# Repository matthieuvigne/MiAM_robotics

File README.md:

# MiAM_robotics

This repo contains information and software for robotic-related projects done with the [MiAM Eurobot team](https://www.miam-robotique.fr/).

Our robot architecture are based off an embedded linux on an ARM platform, Raspberry Pi or Beaglebone Black, programmed
in C++. We also use Arduinos as slaves for low-level tasks such as motor control or sensor handling - using serial communication through
USB.

## Folder structure

 - [miam_utils](./miam_utils) : a very generic C++ library for handling all low-level activities. This ranges from sensor drivers to
 basic robot functions such as PID or basic data logging. This is the base code from which other projects spawn.
 Feel free to use this code in other projects !
 
 - [vacuum_cleaning](./vacuum_cleaning) : our current project, a vacuum-cleaning omnidirectional robot.

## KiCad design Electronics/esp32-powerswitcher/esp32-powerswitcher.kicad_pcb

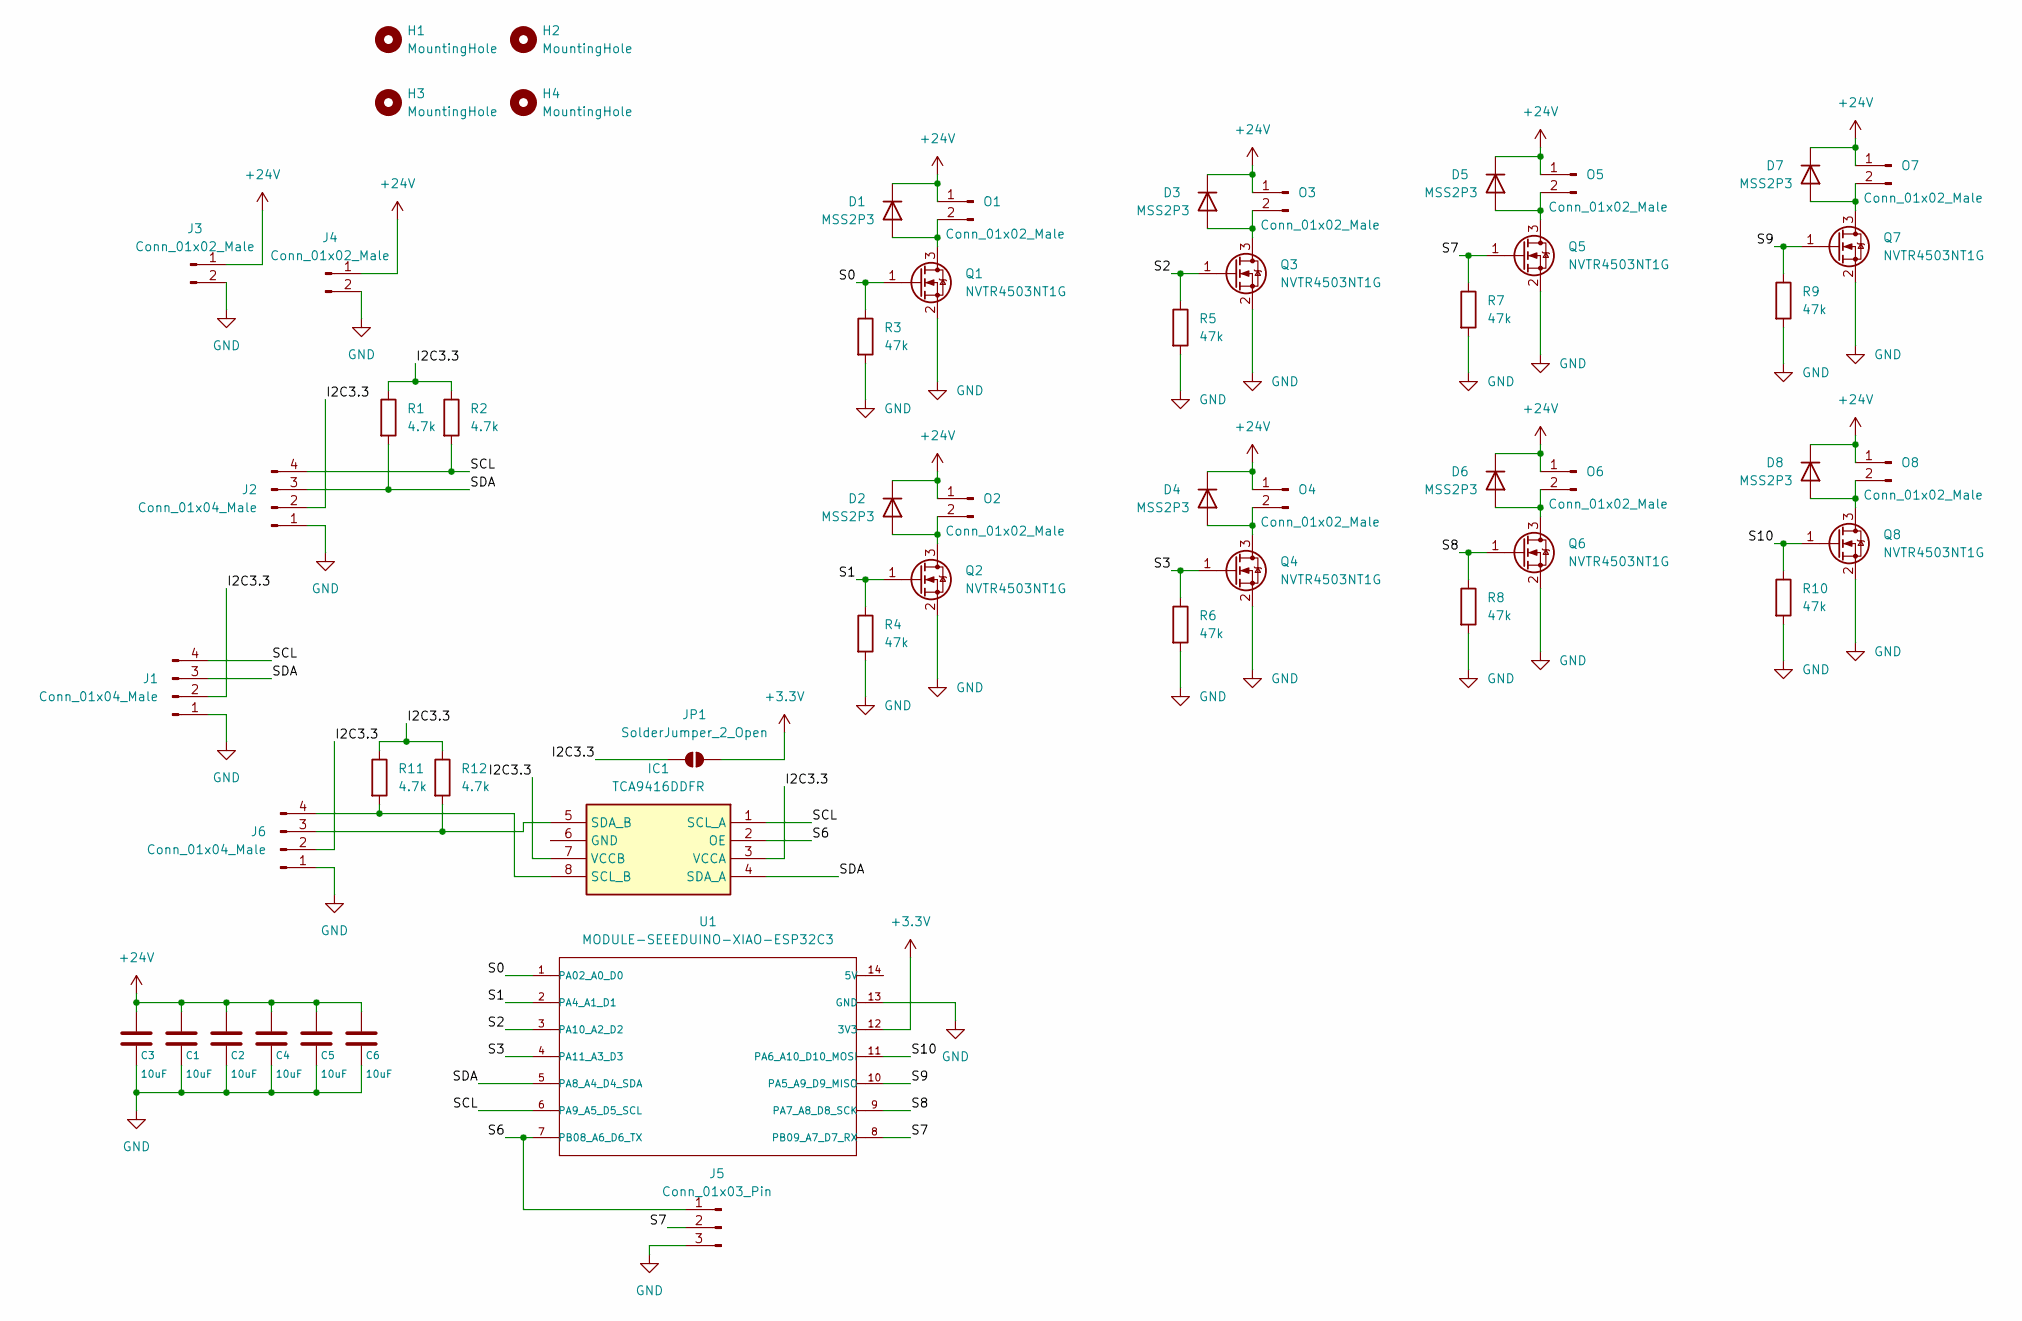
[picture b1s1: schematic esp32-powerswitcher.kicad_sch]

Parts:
C1, C2, C3, C4, C5, C6: 10uF; C_1206_3216Metric_Pad1.33x1.80mm_HandSolder; MPN CL31A106MBHNNNE; Mouser Part Number 187-CL31A106MBHNNNE
D1, D2, D3, D4, D5, D6, D7, D8: MSS2P3; D_MicroSMP_AK
H1, H2, H3, H4: MountingHole; MountingHole_3.2mm_M3
IC1: TCA9416DDFR; SOT65P280X110-8N; Manufacturer_Part_Number TCA9416DDFR; Mouser Part Number 595-TCA9416DDFR
J1, J2, J6: Conn_01x04_Male; JST_SH_SM04B-SRSS-TB_1x04-1MP_P1.00mm_Horizontal
J3, J4: Conn_01x02_Male; XT30UM
J5: Conn_01x03_Pin; PinHeader_1x03_P2.54mm_Vertical
JP1: SolderJumper_2_Open; SolderJumper-2_P1.3mm_Open_Pad1.0x1.5mm
O1, O2, O3, O4, O5, O6, O7, O8: Conn_01x02_Male; JST_PH_B2B-PH-K_1x02_P2.00mm_Vertical; Mouser Part Number 538-53047-0210
Q1, Q2, Q3, Q4, Q5, Q6, Q7, Q8: NVTR4503NT1G; SOT-23_Handsoldering
R1, R2, R11, R12: 4.7k; R_0805_2012Metric_Pad1.20x1.40mm_HandSolder
R3, R4, R5, R6, R7, R8, R9, R10: 47k; R_0805_2012Metric_Pad1.20x1.40mm_HandSolder
U1: MODULE-SEEEDUINO-XIAO-ESP32C3; MODULE14P-SMD-2.54-21X17.8MM

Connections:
+3.3V: JP1.2 (B), U1.12 (3V3)
+24V: C1.1, C2.1, C3.1, C4.1, C5.1, C6.1, D1.1 (K), D2.1 (K), D3.1 (K), D4.1 (K), D5.1 (K), D6.1 (K), D7.1 (K), D8.1 (K), J3.1, J4.1, O1.1, O2.1, O3.1, O4.1, O5.1, O6.1, O7.1, O8.1
/I2C3.3: IC1.3 (VCCA), IC1.7 (VCCB), J1.2, J2.2, J6.2, JP1.1 (A), R1.1, R2.1, R11.1, R12.1
/S0: Q1.1 (G), R3.1, U1.1 (PA02_A0_D0)
/S1: Q2.1 (G), R4.1, U1.2 (PA4_A1_D1)
/S2: Q3.1 (G), R5.1, U1.3 (PA10_A2_D2)
/S3: Q4.1 (G), R6.1, U1.4 (PA11_A3_D3)
/S6: IC1.2 (OE), J5.1, U1.7 (PB08_A6_D6_TX)
/S7: J5.2, Q5.1 (G), R7.1, U1.8 (PB09_A7_D7_RX)
/S8: Q6.1 (G), R8.1, U1.9 (PA7_A8_D8_SCK)
/S9: Q7.1 (G), R9.1, U1.10 (PA5_A9_D9_MISO)
/S10: Q8.1 (G), R10.1, U1.11 (PA6_A10_D10_MOSI)
/SCL: IC1.1 (SCL_A), J1.4, J2.4, R2.2, U1.6 (PA9_A5_D5_SCL)
/SDA: IC1.4 (SDA_A), J1.3, J2.3, R1.2, U1.5 (PA8_A4_D4_SDA)
GND: C1.2, C2.2, C3.2, C4.2, C5.2, C6.2, J1.1, J2.1, J3.2, J4.2, J5.3, J6.1, Q1.2 (S), Q2.2 (S), Q3.2 (S), Q4.2 (S), Q5.2 (S), Q6.2 (S), Q7.2 (S), Q8.2 (S), R3.2, R4.2, R5.2, R6.2, R7.2, R8.2, R9.2, R10.2, U1.13 (GND)
unnamed: D1.2 (A), O1.2, Q1.3 (D)
unnamed: D2.2 (A), O2.2, Q2.3 (D)
unnamed: D3.2 (A), O3.2, Q3.3 (D)
unnamed: D4.2 (A), O4.2, Q4.3 (D)
unnamed: D5.2 (A), O5.2, Q5.3 (D)
unnamed: D6.2 (A), O6.2, Q6.3 (D)
unnamed: D7.2 (A), O7.2, Q7.3 (D)
unnamed: D8.2 (A), O8.2, Q8.3 (D)
unnamed: IC1.8 (SCL_B), J6.4, R11.2
unnamed: IC1.5 (SDA_B), J6.3, R12.2

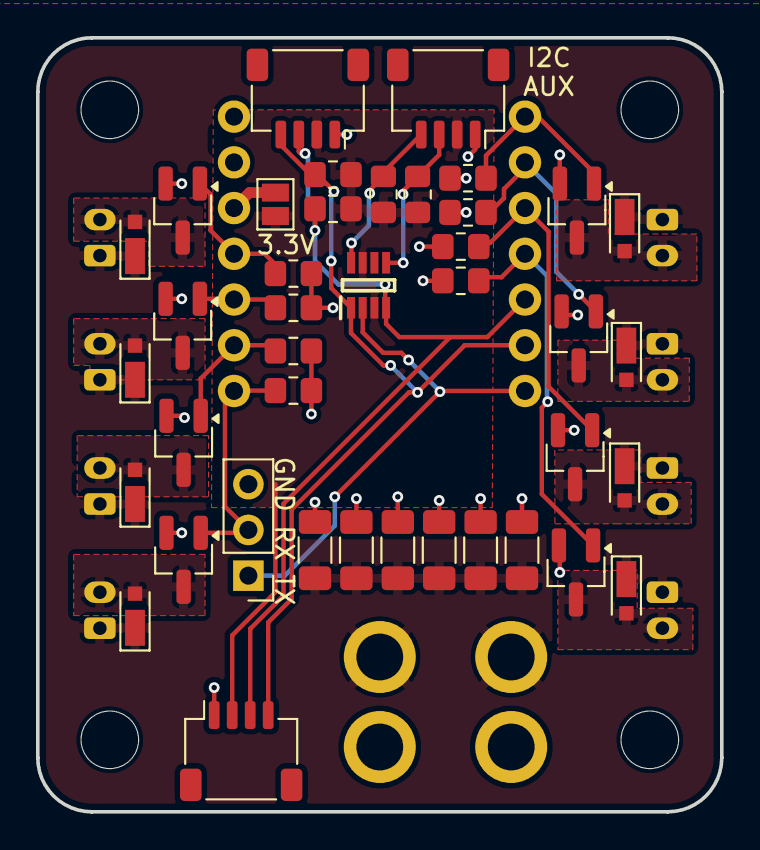
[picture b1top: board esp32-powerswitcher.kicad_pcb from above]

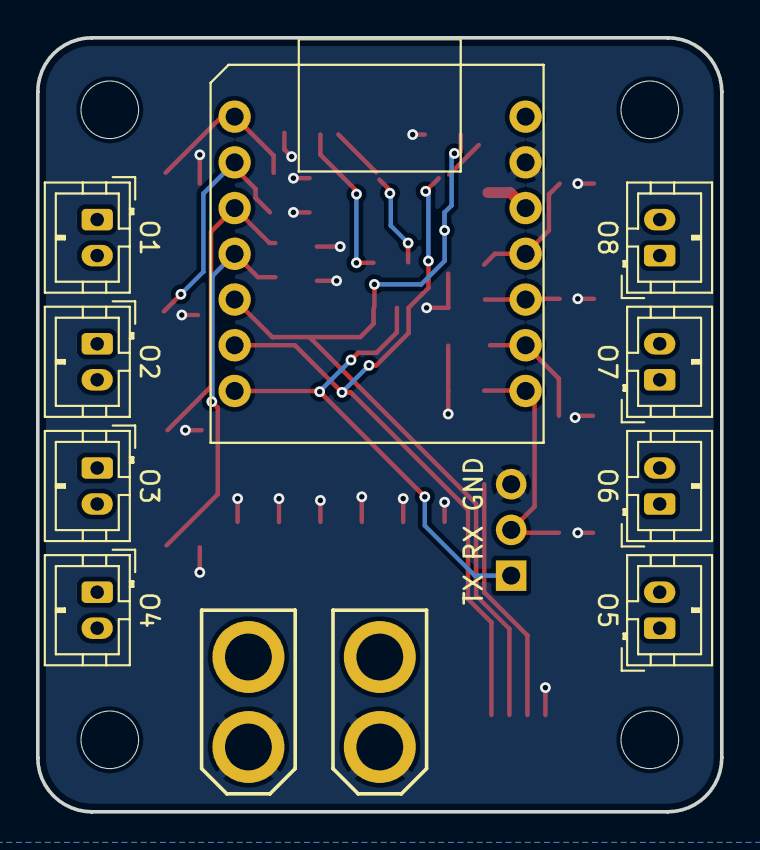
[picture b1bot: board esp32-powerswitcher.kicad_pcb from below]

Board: 2 copper layers, 38.0 x 43.0 mm, 55 parts (11 on the bottom side), 25 nets.

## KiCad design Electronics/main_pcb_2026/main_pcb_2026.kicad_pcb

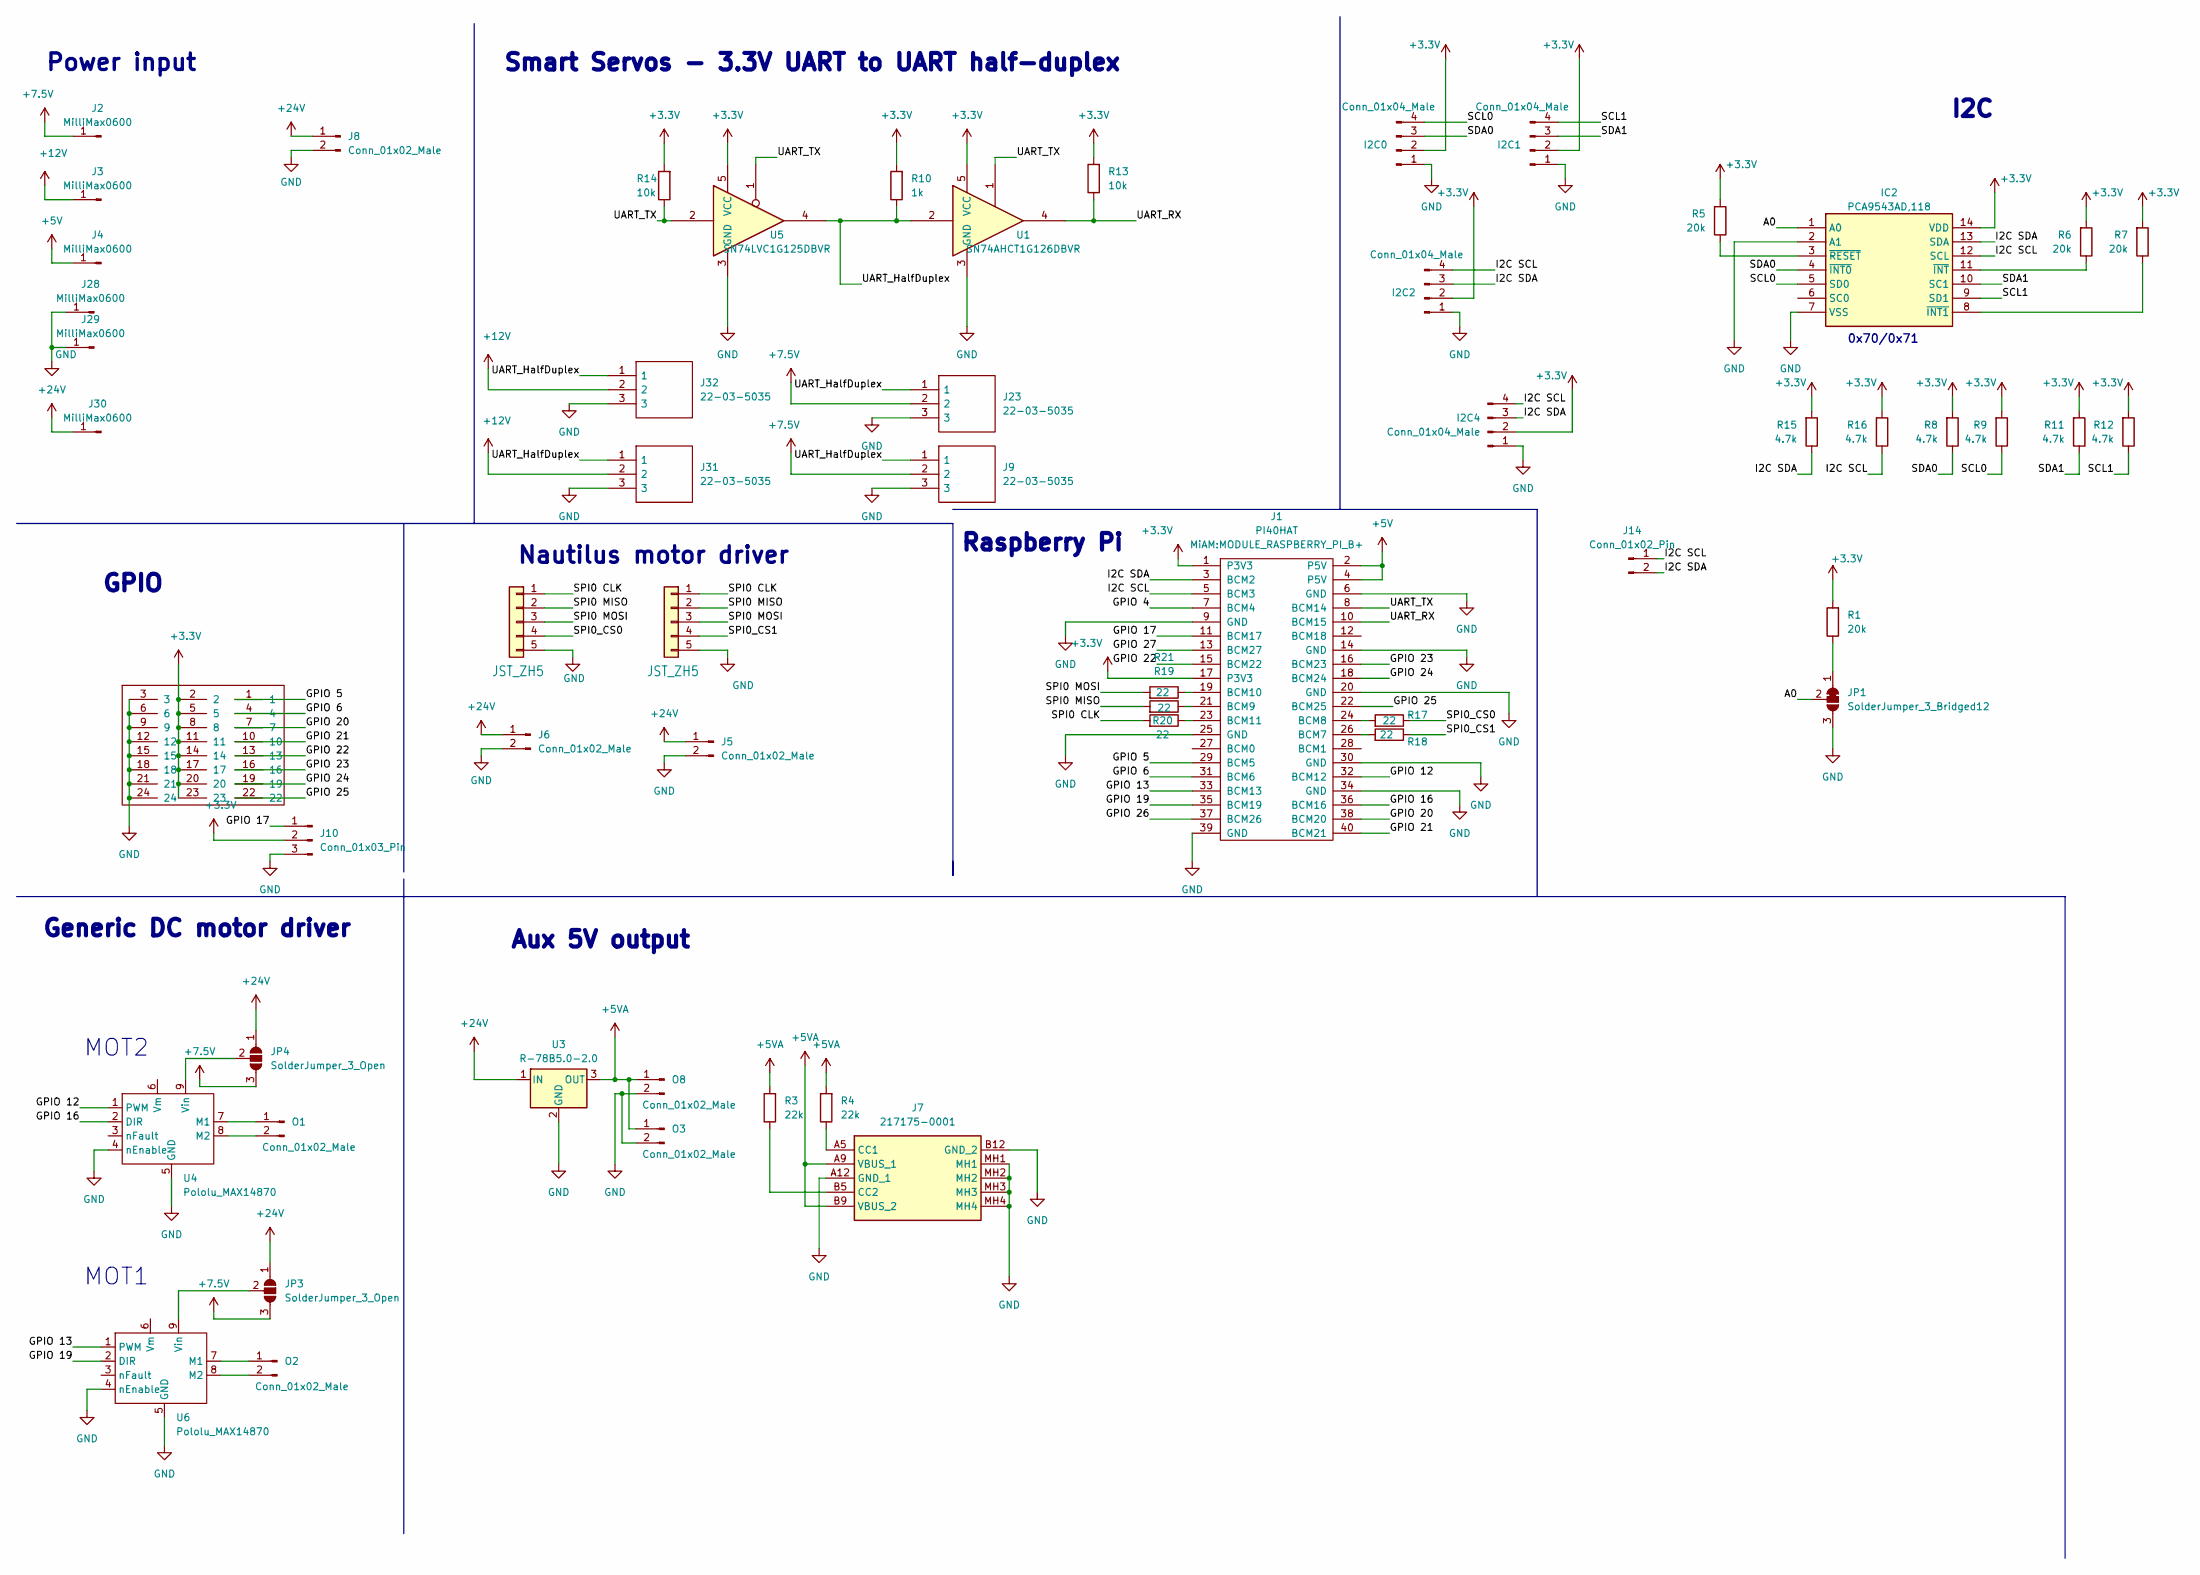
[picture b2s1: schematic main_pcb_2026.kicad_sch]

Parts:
C1: Conn_03x08; Pin_Header_Straight_3x08_Pitch2.54mm
I2C0, I2C1, I2C2, I2C4: Conn_01x04_Male; JST_SH_SM04B-SRSS-TB_1x04-1MP_P1.00mm_Horizontal
IC2: PCA9543AD,118; SOIC127P600X175-14N; Manufacturer_Part_Number PCA9543AD,118; Mouser Part Number 771-PCA9543AD-T
J1: PI40HAT; MODULE_RASPBERRY_PI_B+
J2, J3, J4, J28, J29, J30: MilliMax0600; 0600005150000; Mouser 575-0600005150000
J5, J6, J8: Conn_01x02_Male; XT30UM
J7: 217175-0001; 2171750001; Manufacturer_Part_Number 217175-0001; Mouser Part Number 538-217175-0001
J9, J23, J31, J32: 22-03-5035; SHDR3W60P0X250_1X3_990X490X590P; Manufacturer_Part_Number 22-03-5035
J10: Conn_01x03_Pin; JST_PH_B3B-PH-K_1x03_P2.00mm_Vertical
J14: Conn_01x02_Pin; PogoPin_2.54
JP1: SolderJumper_3_Bridged12; SolderJumper-3_P1.3mm_Bridged12_Pad1.0x1.5mm_NumberLabels
JP3, JP4: SolderJumper_3_Open; SolderJumper-3_P1.3mm_Open_Pad1.0x1.5mm
O1, O2, O3, O8: Conn_01x02_Male; JST_PH_B2B-PH-K_1x02_P2.00mm_Vertical; Mouser Part Number 538-53047-0210
R1, R5, R6, R7: 20k; R_0805_2012Metric
R3, R4: 22k; R_0805_2012Metric
R8, R9, R11, R12, R15, R16: 4.7k; R_0805_2012Metric
R10: 1k; R_0805_2012Metric
R13, R14: 10k; R_0805_2012Metric
R17, R18, R19, R20, R21: 22; R_0805_2012Metric
SPI0, SPI2: JST_ZH5; JST_GH_SM05B-GHS-TB_1x05-1MP_P1.25mm_Horizontal; MPN S4B-ZR-SM4A-TF(LF)(SN)
U1: SN74AHCT1G126DBVR; SOT-23-5_HandSoldering; Mouser Part Number 595-SNAHCT1G126DBVR
U3: R-78B5.0-2.0; Converter_DCDC_RECOM_R-78B-2.0_THT; Mouser R-78B5.0-2.0
U4, U6: Pololu_MAX14870; PololuMAX14870
U5: SN74LVC1G125DBVR; SOT-23-5_HandSoldering; Mouser Part Number 595-SN74LVC1G125DBVR

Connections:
+3.3V: C1.2, C1.5, C1.8, C1.11, C1.14, C1.17, C1.20, C1.23, I2C0.2, I2C1.2, I2C2.2, I2C4.2, IC2.14 (VDD), J1.1 (P3V3), J1.17 (P3V3), J10.2, R1.2, R5.2, R6.2, R7.2, R8.2, R9.2, R10.2, R11.2, R12.2, R13.2, R14.2, R15.2, R16.2, U1.5 (VCC), U5.5 (VCC)
+5V: J1.2 (P5V), J1.4 (P5V), J4.1
+5VA: J7.A9 (VBUS_1), J7.B9 (VBUS_2), O3.1, O8.1, R3.2, R4.2, U3.3 (OUT)
+7.5V: J2.1, J9.2, J23.2, JP3.3 (B), JP4.3 (B)
+12V: J3.1, J31.2, J32.2
+24V: J5.1, J6.1, J8.1, J30.1, JP3.1 (A), JP4.1 (A), U3.1 (IN)
/A0: IC2.1 (A0), JP1.2 (C)
/GPIO 4: J1.7 (BCM4)
/GPIO 5: C1.1, J1.29 (BCM5)
/GPIO 6: C1.4, J1.31 (BCM6)
/GPIO 12: J1.32 (BCM12), U4.1 (PWM)
/GPIO 13: J1.33 (BCM13), U6.1 (PWM)
/GPIO 16: J1.36 (BCM16), U4.2 (DIR)
/GPIO 17: J1.11 (BCM17), J10.1
/GPIO 19: J1.35 (BCM19), U6.2 (DIR)
/GPIO 20: C1.7, J1.38 (BCM20)
/GPIO 21: C1.10, J1.40 (BCM21)
/GPIO 22: C1.13, J1.15 (BCM22)
/GPIO 23: C1.16, J1.16 (BCM23)
/GPIO 24: C1.19, J1.18 (BCM24)
/GPIO 25: C1.22, J1.22 (BCM25)
/GPIO 26: J1.37 (BCM26)
/GPIO 27: J1.13 (BCM27)
/I2C SCL: I2C2.4, I2C4.4, IC2.12 (SCL), J1.5 (BCM3), J14.1, R16.1
/I2C SDA: I2C2.3, I2C4.3, IC2.13 (SDA), J1.3 (BCM2), J14.2, R15.1
/SCL0: I2C0.4, IC2.5 (SD0), R9.1
/SCL1: I2C1.4, IC2.9 (SD1), R12.1
/SDA0: I2C0.3, IC2.4 (~INT0), R8.1
/SDA1: I2C1.3, IC2.10 (SC1), R11.1
/SPI0 CLK: R20.2, SPI0.1, SPI2.1
/SPI0 MISO: R19.2, SPI0.2, SPI2.2
/SPI0 MOSI: R21.2, SPI0.3, SPI2.3
/SPI0_CS0: R17.1, SPI0.4
/SPI0_CS1: R18.1, SPI2.4
/UART_HalfDuplex: J9.1, J23.1, J31.1, J32.1, R10.1, U1.2, U5.4
/UART_RX: J1.10 (BCM15), R13.1, U1.4
/UART_TX: J1.8 (BCM14), R14.1, U1.1, U5.1, U5.2
GND: C1.3, C1.6, C1.9, C1.12, C1.15, C1.18, C1.21, C1.24, I2C0.1, I2C1.1, I2C2.1, I2C4.1, IC2.2 (A1), IC2.7 (VSS), J1.6 (GND), J1.9 (GND), J1.14 (GND), J1.20 (GND), J1.25 (GND), J1.30 (GND), J1.34 (GND), J1.39 (GND), J5.2, J6.2, J7.A12 (GND_1), J7.B12 (GND_2), J7.MH1, J7.MH2, J7.MH3, J7.MH4, J8.2, J9.3, J10.3, J23.3, J28.1, J29.1, J31.3, J32.3, JP1.3 (B), O3.2, O8.2, SPI0.5, SPI2.5, U1.3 (GND), U3.2 (GND), U4.4 (nEnable), U4.5 (GND), U5.3 (GND), U6.4 (nEnable), U6.5 (GND)
unnamed: IC2.8 (~INT1), R7.1
unnamed: IC2.11 (~INT), R6.1
unnamed: IC2.3 (~RESET), R5.1
unnamed: J1.26 (BCM7), R18.2
unnamed: J1.24 (BCM8), R17.2
unnamed: J1.21 (BCM9), R19.1
unnamed: J1.19 (BCM10), R21.1
unnamed: J1.23 (BCM11), R20.1
unnamed: J7.A5 (CC1), R4.1
unnamed: J7.B5 (CC2), R3.1
unnamed: JP1.1 (A), R1.1
unnamed: JP3.2 (C), U6.9 (Vin)
unnamed: JP4.2 (C), U4.9 (Vin)
unnamed: O1.1, U4.7 (M1)
unnamed: O1.2, U4.8 (M2)
unnamed: O2.1, U6.7 (M1)
unnamed: O2.2, U6.8 (M2)

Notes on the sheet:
0x70/0x71
Nautilus motor driver
GPIO
I2C
MOT1
Smart Servos - 3.3V UART to UART half-duplex
Power input
Aux 5V output
Generic DC motor driver
MOT2
Raspberry Pi

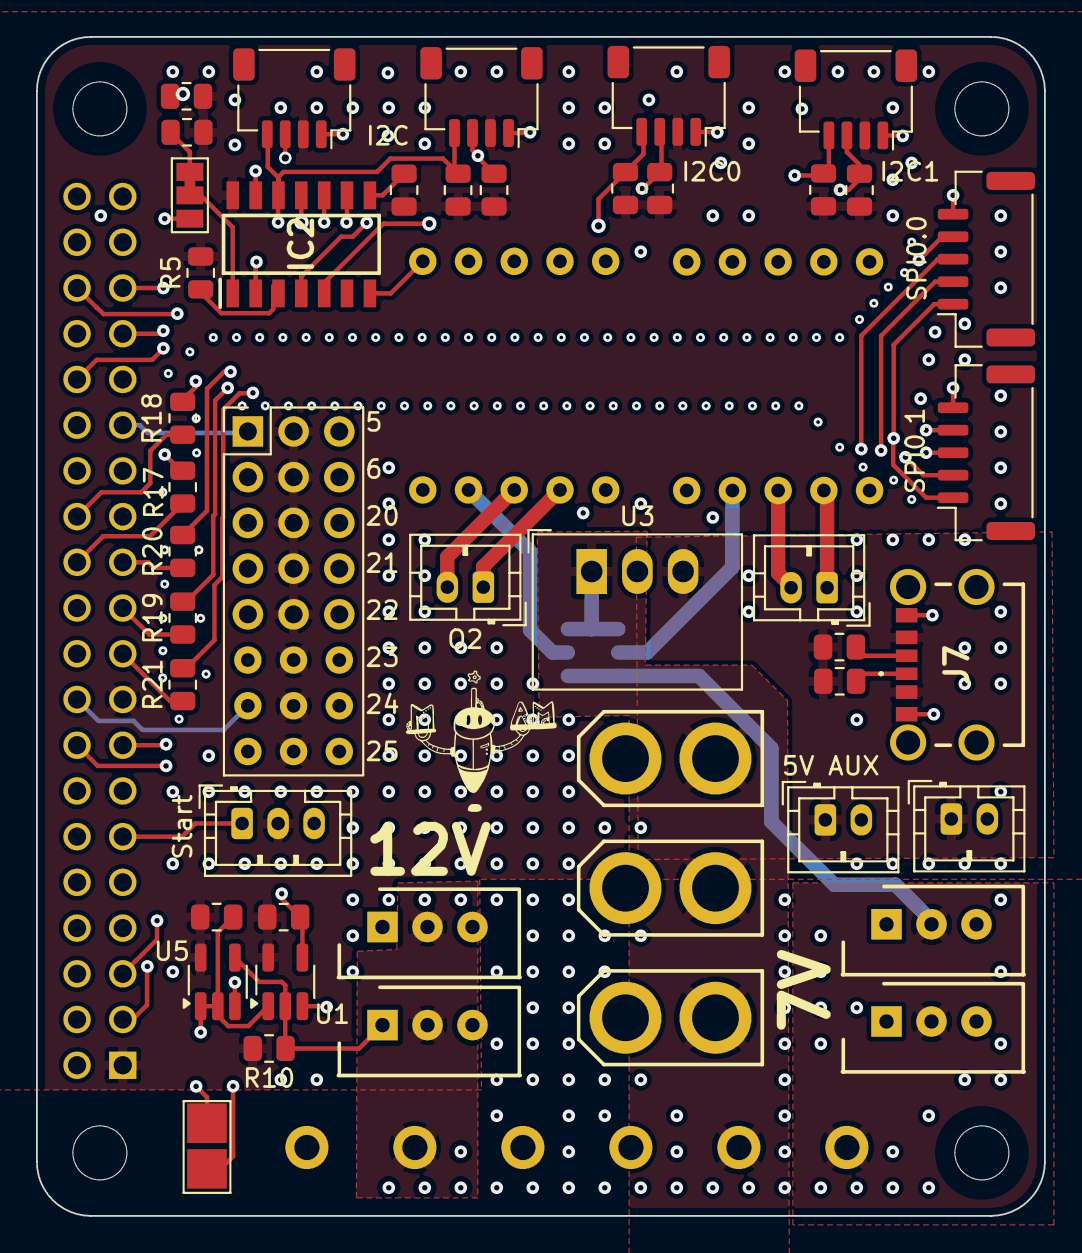
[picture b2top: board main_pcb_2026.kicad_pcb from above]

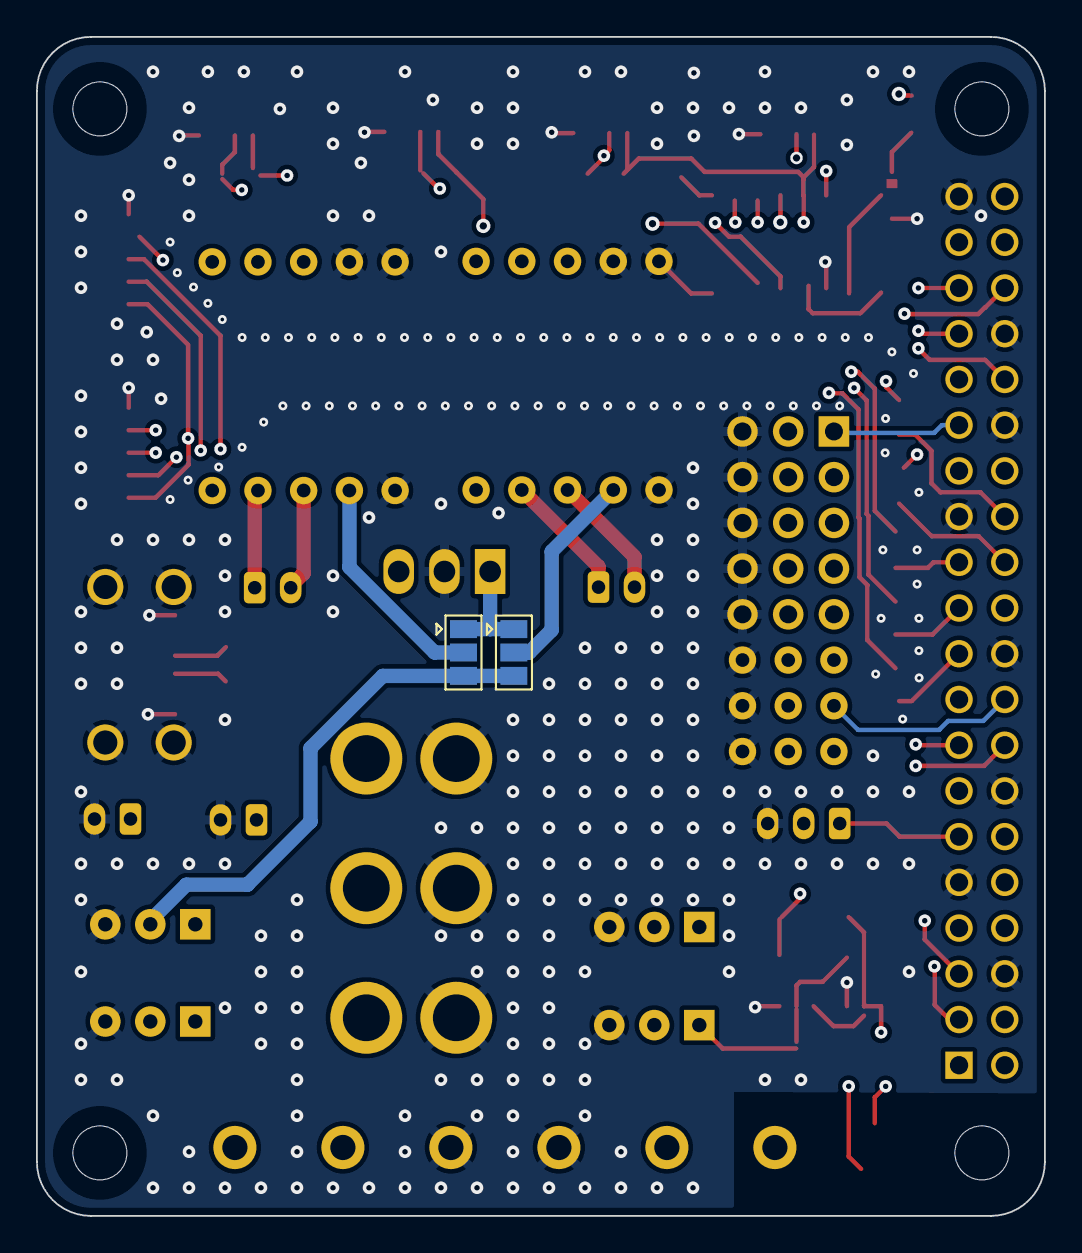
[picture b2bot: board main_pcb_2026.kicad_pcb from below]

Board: 4 copper layers, 56.0 x 65.5 mm, 57 parts (2 on the bottom side), 52 nets.
